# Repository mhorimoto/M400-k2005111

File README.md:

# 音声切り替え装置 (A26)
# K2005111

# 要求するHardware

- Arduino Nano V3
- 8ch Relay module
- I2C LCD 1602A (Address:0x27)

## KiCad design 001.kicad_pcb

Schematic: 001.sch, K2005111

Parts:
C1: 10uF; CP_Radial_D5.0mm_P2.00mm
C2: 0.1uF; C_Disc_D5.0mm_W2.5mm_P2.50mm
CN1: PWR5V; B02B-XH
CN2: JD-VCC; B02B-XH
CN3: TO-RLY; B10B-XH
CN4: I2C-LCD; B04B-XH
CN5: INPUT-A; B02B-XH
CN6: INPUT-B; B02B-XH
CN7: INPUT-C; B02B-XH
CN8: BTN-A; B02B-XH
CN9: BTN-B; B02B-XH
CN10: BTN-C; B02B-XH
CN11: BTN-STOP; B02B-XH
CN12: DELAY-VR; B03B-XH
D1, D2, D3, D4, D5: 1N4007; D_DO-41_SOD81_P10.16mm_Horizontal
M1: ARDUINO-NANO-3.0
R1, R2, R3: 4.7k; R_Axial_DIN0207_L6.3mm_D2.5mm_P10.16mm_Horizontal
RV1, RV2, RV3, RV4, RV5, RV6: TNR10V471K; RV_Disc_D12mm_W3.9mm_P7.5mm
U1, U2, U3: TOSHIBA_TLP222A; TOSHIBA_TLP222A_F_0

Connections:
3V3: M1.J2.14 (3V3)
/5V_JDV: CN2.P$1, D2.1 (K)
/5V_M: C1.1, C2.1, CN1.P$1, D1.2 (A), D2.2 (A)
/5V_MPU: CN3.P$10, CN4.P$3, CN12.P$1, D1.1 (K), D3.2 (A), D4.2 (A), D5.2 (A), M1.J2.4 (5V)
GND: C1.2, C2.2, CN1.P$2, CN2.P$2, CN4.P$4, CN8.P$2, CN9.P$2, CN10.P$2, CN11.P$2, CN12.P$3, M1.J1.4 (GND.1), M1.J2.2 (GND.2), RV2.2, RV4.2, RV6.2, U1.2 (CATHODE), U1.3 (1_DRAIN), U2.2 (CATHODE), U2.3 (1_DRAIN), U3.2 (CATHODE), U3.3 (1_DRAIN)
unnamed: CN3.P$2, CN3.P$3, M1.J1.8 (D5)
unnamed: CN3.P$4, CN3.P$5, M1.J1.7 (D4)
unnamed: CN3.P$6, CN3.P$7, M1.J1.6 (D3)
unnamed: CN3.P$8, CN3.P$9, M1.J1.5 (D2)
unnamed: CN4.P$1, M1.J2.7 (A5)
unnamed: CN4.P$2, M1.J2.8 (A4)
unnamed: CN5.P$1, R1.1, RV1.2, RV2.1
unnamed: CN5.P$2, D3.1 (K), RV1.1
unnamed: CN6.P$1, R2.1, RV3.2, RV4.1
unnamed: CN6.P$2, D4.1 (K), RV3.1
unnamed: CN7.P$1, R3.1, RV5.2, RV6.1
unnamed: CN7.P$2, D5.1 (K), RV5.1
unnamed: CN8.P$1, M1.J1.15 (D12/MISO)
unnamed: CN9.P$1, M1.J1.14 (D11/MOSI)
unnamed: CN10.P$1, M1.J2.15 (D13/SCK)
unnamed: CN11.P$1, M1.J1.13 (D10)
unnamed: CN12.P$2, M1.J2.12 (A0)
unnamed: M1.J1.1 (D1/TX), U1.4 (2_DRAIN)
unnamed: M1.J1.2 (D0/RX), U2.4 (2_DRAIN)
unnamed: M1.J1.12 (D9), U3.4 (2_DRAIN)
unnamed: R1.2, U1.1 (ANODE)
unnamed: R2.2, U2.1 (ANODE)
unnamed: R3.2, U3.1 (ANODE)
VIN: M1.J2.1 (VIN)

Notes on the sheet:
MODEL-400 K2005111

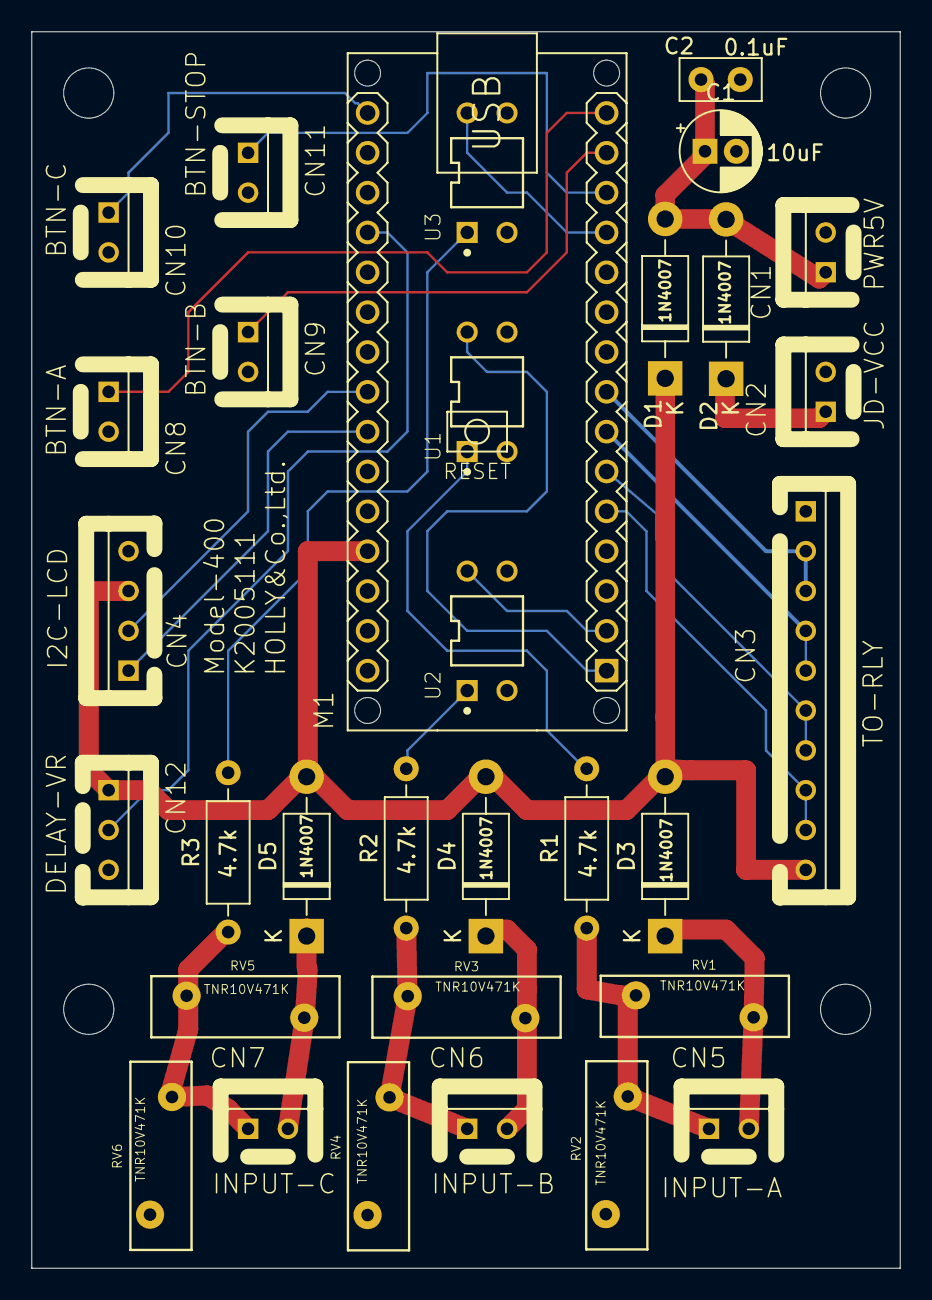
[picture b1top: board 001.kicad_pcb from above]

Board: 2 copper layers, 55.4 x 78.8 mm, 32 parts (0 on the bottom side), 27 nets.

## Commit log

2020-06-15 1N4007に変更
2020-06-19 ソースコードと一緒に管理
2020-06-19 A11 Remote Mode中にSTOPボタンが効くようにする予定
2020-06-21 CAM初版
2020-06-22 ヴァリスタ追加
2020-06-25 KiCADへ移行
2020-06-26 foot printを見直し中
2020-06-27 ガーバーデータも出来た
2020-06-30 GBR初版
2020-07-19 fp-info-cacheが更新されてた
2020-07-19 Arduino IDEに合わせでプログラムを移動
2020-07-21 REMOTE MODEのinstsをswitch()する部分から
2020-07-22 program.ino途中
2020-07-22 A26版でほぼ完成。未検証
2020-07-24 PCBGOGOへ入稿
2020-07-27 GBR出し直し
2020-07-27 RS-274XでX2オプション外してドリル穴は１ファイル化
2020-08-08 フレームを追加とケースの加工データ
2020-08-31 VR取付支持台を作成
2020-09-01 A27 リリースかな。
2020-09-02 KiCAD用ignore file追加
2021-06-14 somthings
2021-06-15 debug:A28 remove serial operation
